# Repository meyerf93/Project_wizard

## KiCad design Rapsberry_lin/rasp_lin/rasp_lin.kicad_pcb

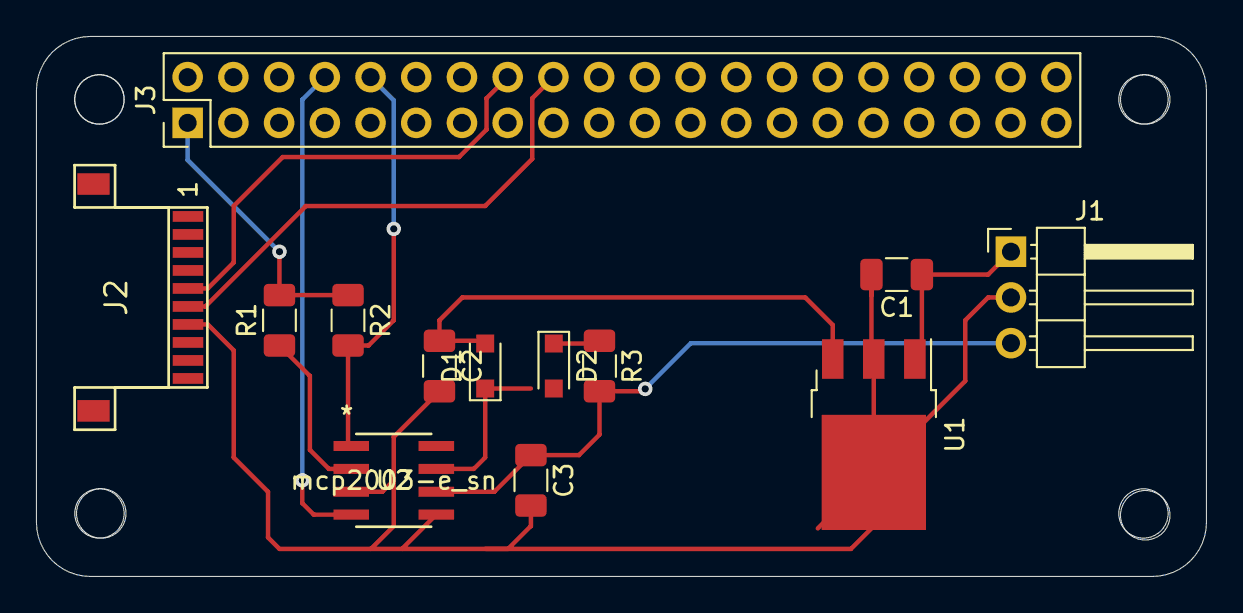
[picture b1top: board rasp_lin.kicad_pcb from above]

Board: 2 copper layers, 65.0 x 30.0 mm, 13 parts (0 on the bottom side), 12 nets.

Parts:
C1: 0.33uF; C_1206_3216Metric
C2: 0.1uF; C_1206_3216Metric
C3: 220pF; C_1206_3216Metric
D1, D2: 1N4148; D_SOD-323_HandSoldering
J1: Interface; Pin_Header_Angled_1x03_Pitch2.54mm
J2: FFC; TE FFC_10 Footprint
J3: Conn_02x20_Odd_Even; PinHeader_2x20_P2.54mm_Vertical
R1, R2: 4.7k; R_1206_3216Metric
R3: 1k; R_1206_3216Metric
U1: L7812; TO-252-3_TabPin2
U2: mcp2003-e_sn; mcp2003-e&slash_sn

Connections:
+3V3: J3.1, R1.2, R2.1
+12V: C2.1, D1.2, U1.3
+24V: C1.1, J1.1, U1.1
Bdown: J2.6, J3.18
Bup: J2.5, J3.16
GND: C1.2, C2.2, C3.2, J1.2, J2.7, U1.2, U2.3, U2.5
LINBUS: C3.1, J1.3, R3.2, U2.6
unnamed: D1.1, D2.2, U2.7
unnamed: D2.1, R3.1
unnamed: J3.8, U2.4
unnamed: J3.10, R2.2, U2.1
unnamed: R1.1, U2.2

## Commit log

2019-12-14 init commit
2020-03-05 add ikea code
2021-09-01 add new project

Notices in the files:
Rapsberry_lin/rasp_lin/rasp_lin.kicad_pcb:
License: MIT - Copyright 2018 StudioPieters®
parts and their libraries:
Copyright 2016 Accelerated Designs. All rights reserved.
